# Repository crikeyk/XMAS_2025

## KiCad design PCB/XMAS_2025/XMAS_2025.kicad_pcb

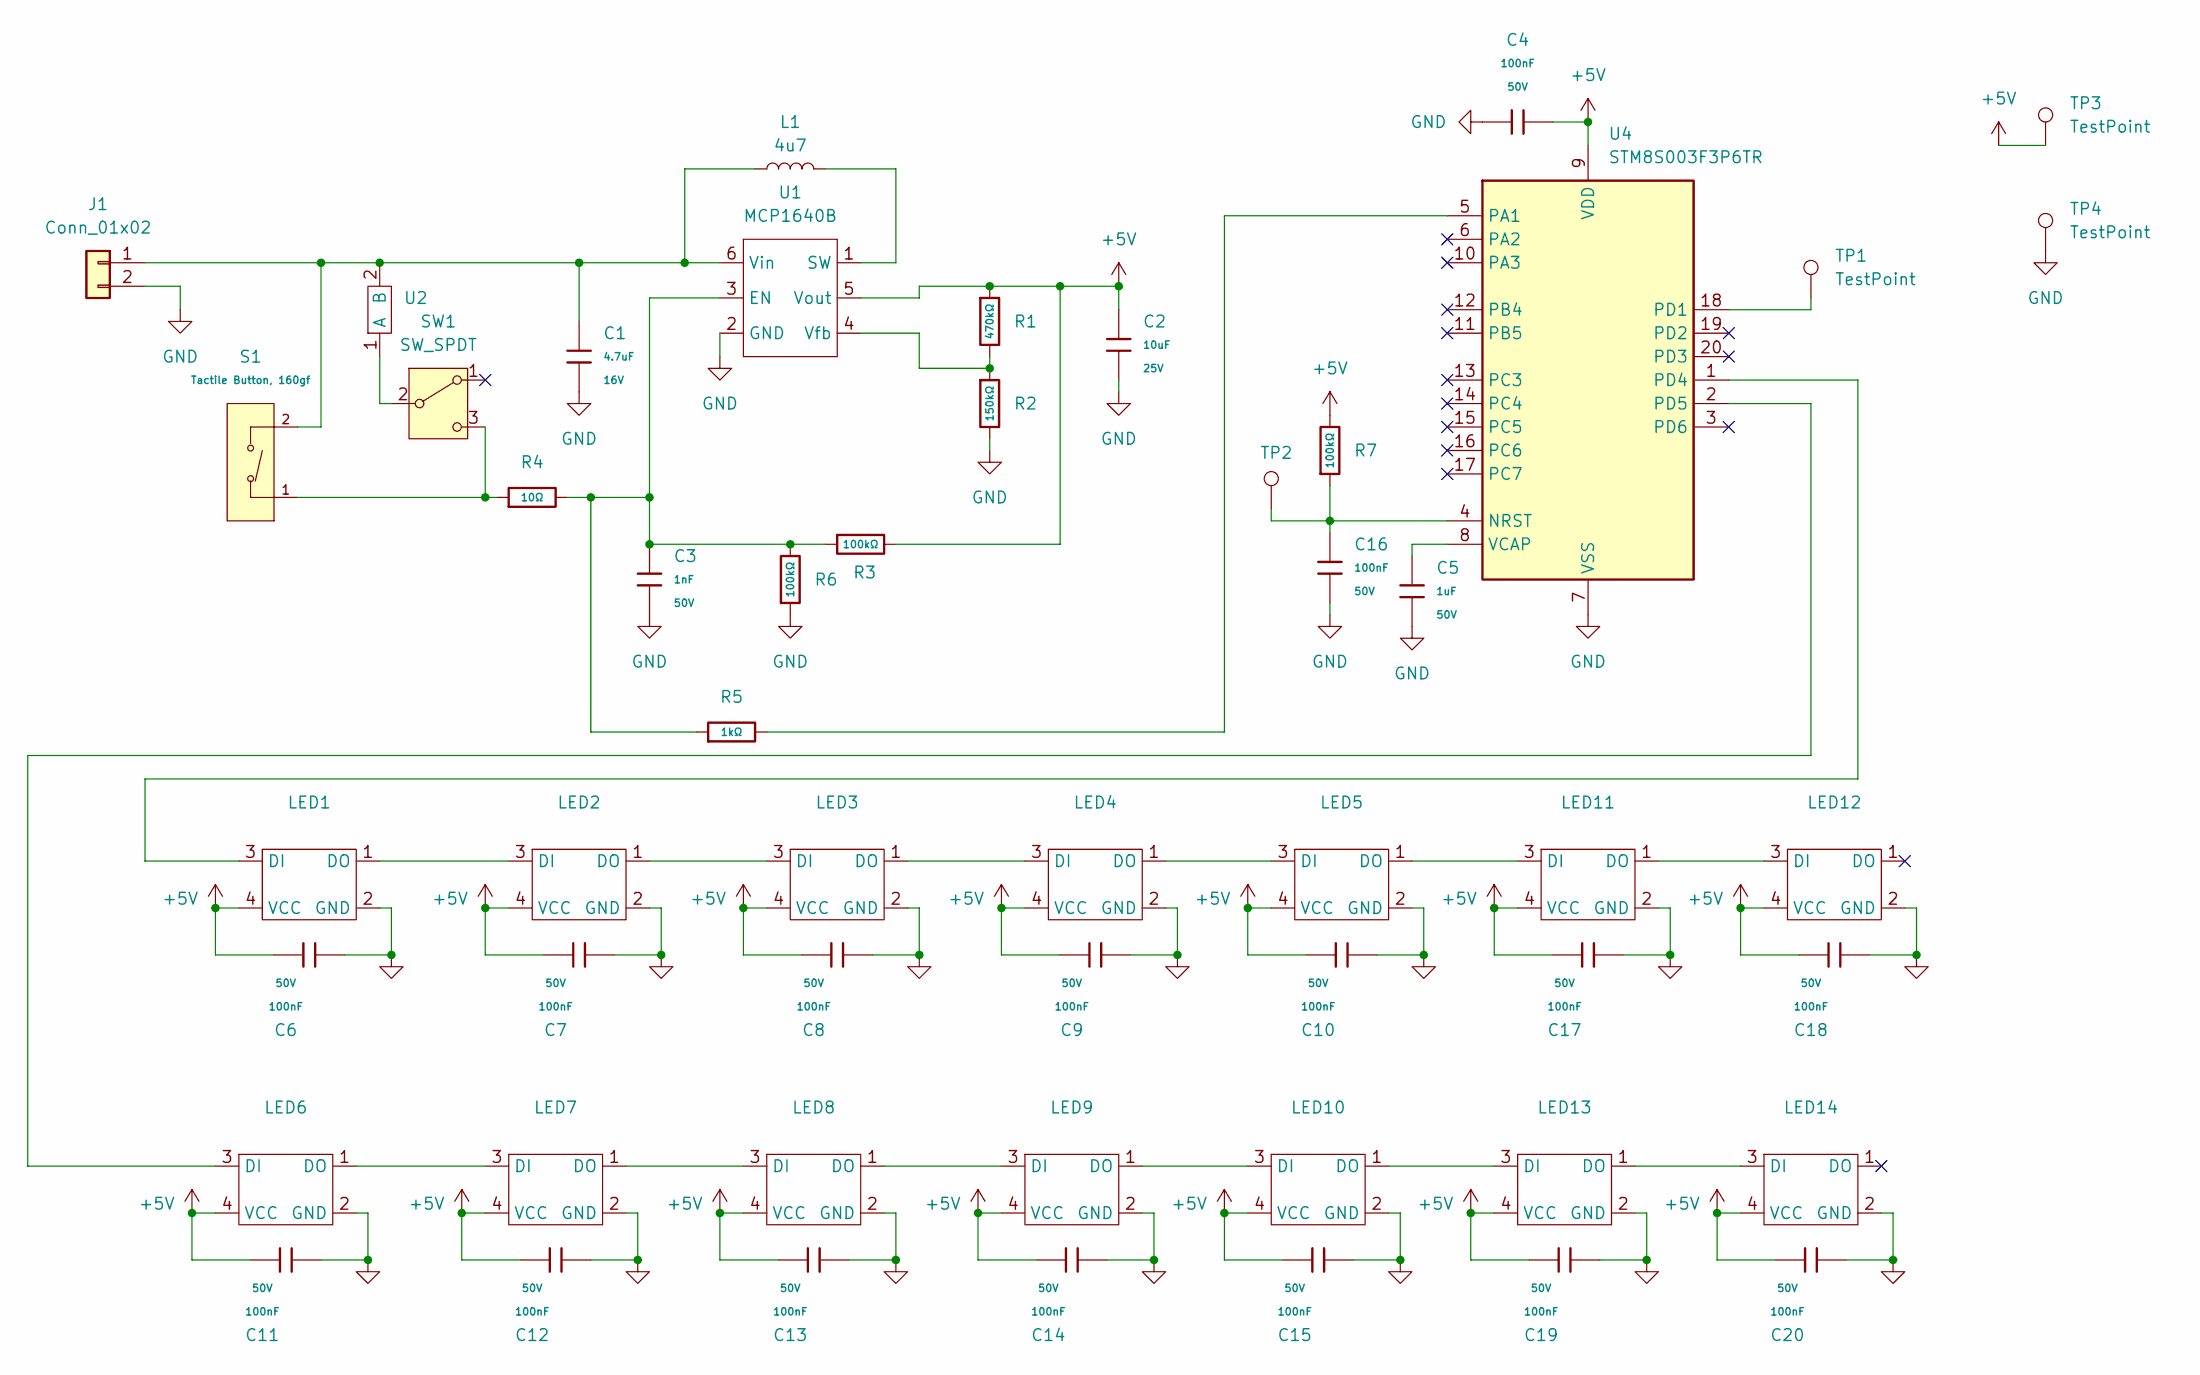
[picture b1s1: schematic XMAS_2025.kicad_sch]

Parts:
C1: 4.7uF; C_0603; Voltage Rated 16V; Tolerance ±10%; Part CL10A475KO8NNNC; LCSC C19666
C2: 10uF; C_0805; Voltage Rated 25V; Tolerance ±10%; Part CL21A106KAYNNNE; LCSC C15850
C3: 1nF; C_0603; Voltage Rated 50V; Tolerance ±10%; Part CL10B102KB8NNNC; LCSC C1588
C4, C6, C7, C8, C9, C10, C11, C12, C13, C14, C15, C16, C17, C18, C19, C20: 100nF; C_0603; Voltage Rated 50V; Tolerance ±10%; Part CC0603KRX7R9BB104; LCSC C14663
C5: 1uF; C_0603; Voltage Rated 50V; Tolerance ±10%; Part CL10A105KB8NNNC; LCSC C15849
J1: Conn_01x02; AAA cutout
L1: 4u7; L_APV_ANR3015; LCSC C7427089
LED1, LED2, LED3, LED4, LED5, LED6, LED7, LED8, LED9, LED10, LED11, LED12, LED13, LED14: WS2812_2020; LCSC C965555
R1: 470kΩ; R_0603; Overload Voltage (Max) 75V; Tolerance ±1%; Part 0603WAF4703T5E; LCSC C23178
R2: 150kΩ; R_0603; Overload Voltage (Max) 75V; Tolerance ±1%; Part 0603WAF1503T5E; LCSC C22807
R3, R6, R7: 100kΩ; R_0603; Overload Voltage (Max) 75V; Tolerance ±1%; Part 0603WAF1003T5E; LCSC C25803
R4: 10Ω; R_0603; Overload Voltage (Max) 75V; Tolerance ±1%; Part 0603WAF100JT5E; LCSC C22859
R5: 1kΩ; R_0603; Overload Voltage (Max) 75V; Tolerance ±1%; Part 0603WAF1001T5E; LCSC C21190
S1: Tactile Button, 160gf; SW_TS-1088-AR02016; Voltage Rating (Dc) 12V; Part TS-1088-AR02016; LCSC C720477
SW1: SW_SPDT; SW_SPDT_PCM12; LCSC C778186
TP1, TP2, TP3, TP4: TestPoint; TestPoint_Pad_D2.0mm
U1: MCP1640B; SOT-23-6; LCSC C478087
U2: R_Axial_DIN0204_L3.6mm_D1.6mm_P1.90mm_Vertical; LCSC C2879950
U4: STM8S003F3P6TR; TSSOP-20_4.4x6.5mm_P0.65mm; Operating Voltage Range 2.95V~5.5V; Low Voltage Detection T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 2.95V~5.5V; Part STM8S003F3P6TR; LCSC C52717

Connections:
+5V: C2.1, C4.2, C6.2, C7.2, C8.2, C9.2, C10.2, C11.2, C12.2, C13.2, C14.2, C15.2, C17.2, C18.2, C19.2, C20.2, LED1.4 (VCC), LED2.4 (VCC), LED3.4 (VCC), LED4.4 (VCC), LED5.4 (VCC), LED6.4 (VCC), LED7.4 (VCC), LED8.4 (VCC), LED9.4 (VCC), LED10.4 (VCC), LED11.4 (VCC), LED12.4 (VCC), LED13.4 (VCC), LED14.4 (VCC), R1.1, R3.2, R7.2, TP3.1, U1.5 (Vout), U4.9 (VDD)
GND: C1.2, C2.2, C3.2, C4.1, C5.2, C6.1, C7.1, C8.1, C9.1, C10.1, C11.1, C12.1, C13.1, C14.1, C15.1, C16.2, C17.1, C18.1, C19.1, C20.1, J1.2, LED1.2 (GND), LED2.2 (GND), LED3.2 (GND), LED4.2 (GND), LED5.2 (GND), LED6.2 (GND), LED7.2 (GND), LED8.2 (GND), LED9.2 (GND), LED10.2 (GND), LED11.2 (GND), LED12.2 (GND), LED13.2 (GND), LED14.2 (GND), R2.2, R6.1, TP4.1, U1.2 (GND), U4.7 (VSS)
unnamed: C1.1, J1.1, L1.1, S1.2 (B), U1.6 (Vin), U2.2 (B)
unnamed: LED1.3 (DI), U4.1 (PD4)
unnamed: LED1.1 (DO), LED2.3 (DI)
unnamed: LED2.1 (DO), LED3.3 (DI)
unnamed: LED3.1 (DO), LED4.3 (DI)
unnamed: LED4.1 (DO), LED5.3 (DI)
unnamed: LED6.3 (DI), U4.2 (PD5)
unnamed: LED6.1 (DO), LED7.3 (DI)
unnamed: LED7.1 (DO), LED8.3 (DI)
unnamed: LED8.1 (DO), LED9.3 (DI)
unnamed: LED9.1 (DO), LED10.3 (DI)
unnamed: LED10.1 (DO), LED13.3 (DI)
unnamed: LED5.1 (DO), LED11.3 (DI)
unnamed: LED11.1 (DO), LED12.3 (DI)
unnamed: LED13.1 (DO), LED14.3 (DI)
unnamed: R4.1, S1.1 (A), SW1.3 (C)
unnamed: SW1.2 (B), U2.1 (A)
unnamed: C3.1, R3.1, R4.2, R5.1, R6.2, U1.3 (EN)
unnamed: L1.2, U1.1 (SW)
unnamed: R1.2, R2.1, U1.4 (Vfb)
unnamed: C16.1, R7.1, TP2.1, U4.4 (NRST)
unnamed: R5.2, U4.5 (PA1)
unnamed: TP1.1, U4.18 (PD1)
unnamed: C5.1, U4.8 (VCAP)

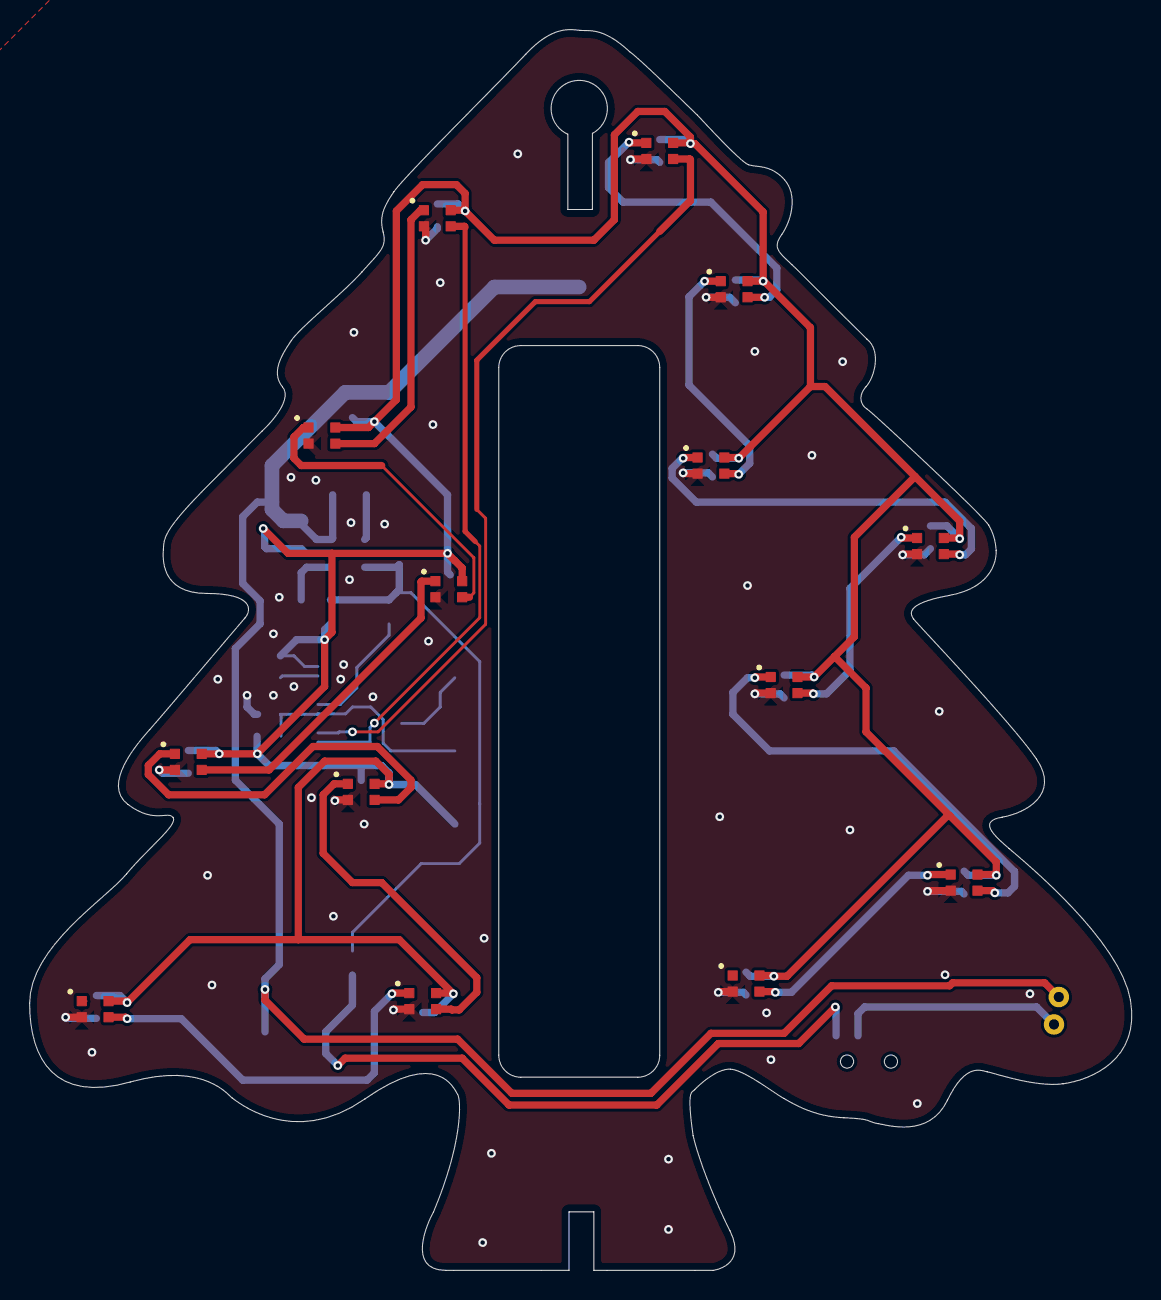
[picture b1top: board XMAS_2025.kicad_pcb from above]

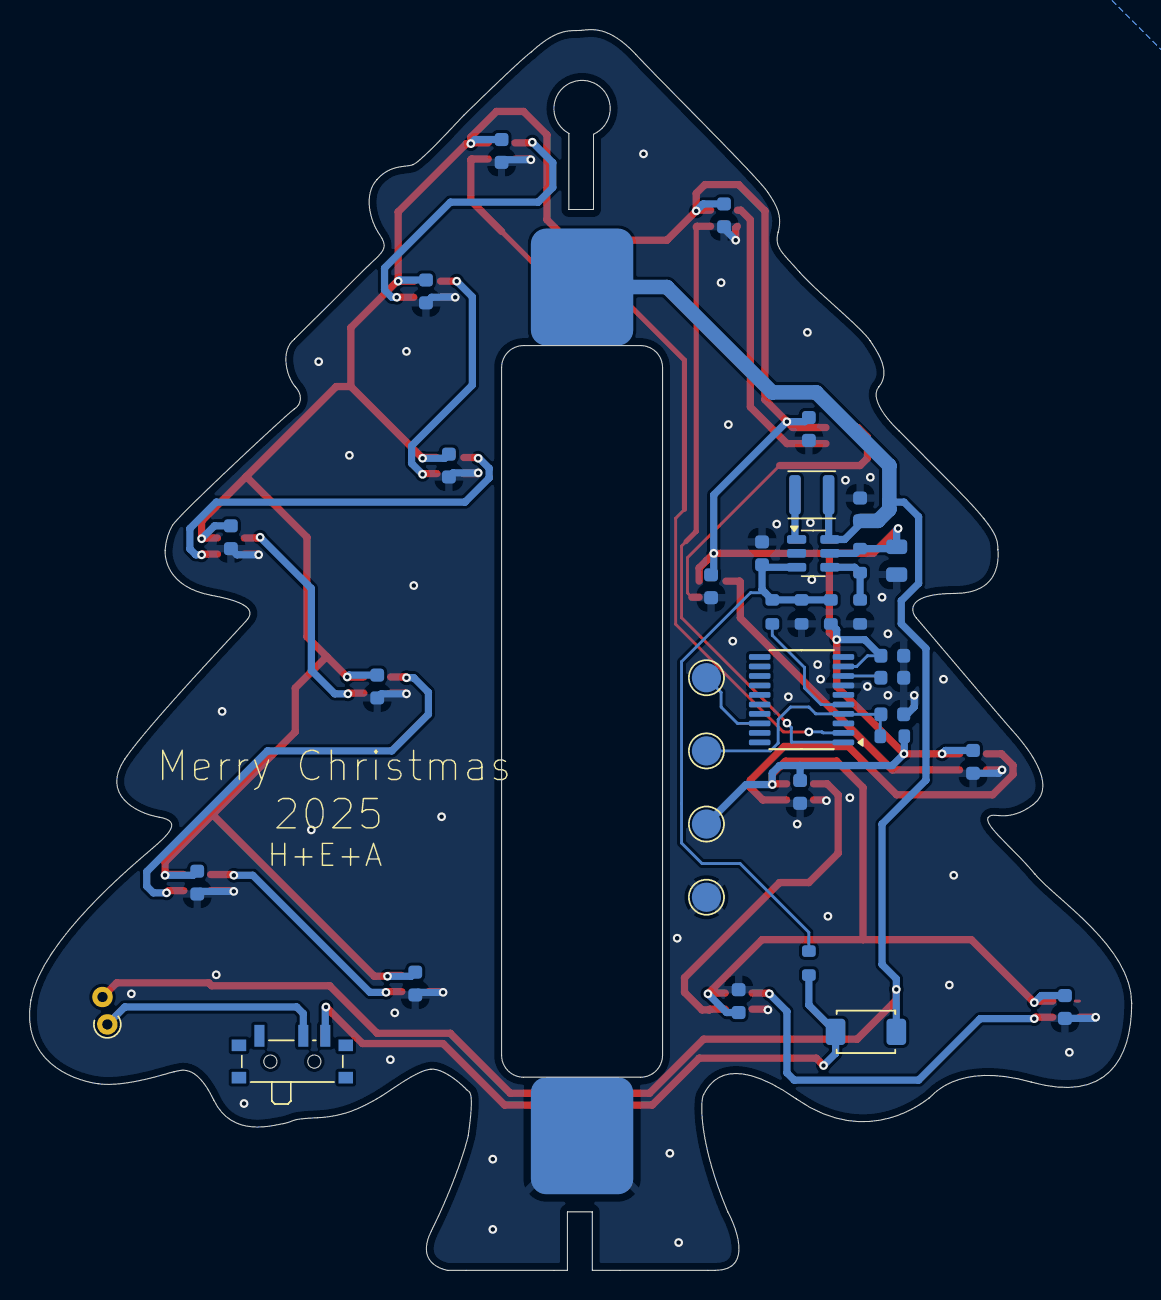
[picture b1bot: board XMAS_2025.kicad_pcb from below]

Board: 2 copper layers, 75.3 x 84.8 mm, 52 parts (38 on the bottom side), 26 nets.

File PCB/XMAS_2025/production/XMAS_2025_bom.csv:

Designator,Footprint,Quantity,Value,LCSC Part #
C1,C_0603,1,4.7uF,C19666
"C10, C11, C12, C13, C14, C15, C16, C17, C18, C19, C20, C4, C6, C7, C8, C9",C_0603,16,100nF,C14663
C2,C_0805,1,10uF,C15850
C3,C_0603,1,1nF,C1588
C5,C_0603,1,1uF,C15849
L1,L_APV_ANR3015,1,4u7,C7427089
"LED1, LED10, LED11, LED12, LED13, LED14, LED2, LED3, LED4, LED5, LED6, LED7, LED8, LED9",WS2812_2020,14,~,C965555
R1,R_0603,1,470kΩ,C23178
R2,R_0603,1,150kΩ,C22807
"R3, R6, R7",R_0603,3,100kΩ,C25803
R4,R_0603,1,10Ω,C22859
R5,R_0603,1,1kΩ,C21190
S1,SW_TS-1088-AR02016,1,"Tactile Button, 160gf",C720477
SW1,SW_SPDT_PCM12,1,SW_SPDT,C778186
U1,SOT-23-6,1,MCP1640B,C478087
U4,TSSOP-20_4.4x6.5mm_P0.65mm,1,STM8S003F3P6TR,C52717

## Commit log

2025-08-30 added firmware placeholder
2025-11-21 released for fab
2025-12-18 added firmware
